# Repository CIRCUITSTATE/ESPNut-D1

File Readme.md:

# ESPNut-D1

[**ESPNut-D1**](https://github.com/CIRCUITSTATE/ESPNut-D1) (pronounced as **"ee yes peanut"**) is a single-channel USB-to-Serial converter and Auto-Programmer for the ESP32 & ESP8266 series microcontrollers from Espressif. While there exists many such programmers, ESPNut-D1 is a completely open-source hardware (OSHW) project designed in the **KiCad** open-source EDA tool. **D1** is the first design variant of this project. You can download the source files of this design, modify them and redistribute them as you wish.

ESPNut-D1 is based on the popular **CH340** series USB-to-Serial converter chip from *WCH*. The serial port of the chip connects to the target microcontroller through its own serial port. Thanks to the built-in serial bootloader of the ESP series microcontrollers, you can effortlessly program them at any time. The ESPNut-D1 makes this process a bit more convenient.

## Features

- CH340C/CH340G USB-to-Serial converter chip.
  - No external crystal required for the CH340C.
- USB-C connector with extra solderpads.
- Auto bootloader and reset circuit. Control both functions from the USB.
- Dedicated push-buttons for target reset and boot mode.
- 3.6~12V in, 3.3V out, 500 mA LDO.
- Slide switch for target power control.
- Target power control through load switch.
- SPDT slide switch for target voltage selection. Select between 3.3V and 5V.
- VBUS and target power indication LEDs.
- UART activity LEDs for both `TX` and `RX` lines.
- Dedicated push-button for power control of the target. Useful for boards without reset pin.
- 6-pin ESP-PROG 1.27 mm header.
- 6-pin JST-SH connector and solderpad for target ESP.
- 2x M2 mounting holes.

## Design

- **Parent Project:** ESPNut
- **Variant:** [ESPNut-D1](https://github.com/CIRCUITSTATE/ESPNut-D1)
- **Author:** Vishnu Mohanan (@vishnumaiea)
- **Latest Revision:** `R0.4`
- **Layer Count:** 2
- **Thickness:** 1.6 mm
- **Dimensions:** 44 x 20 mm
- **EDA Tool:** KiCad V9
- **License:** MIT

## Contributing

If you would like to contribute this project, you are welcome to post issues and feature requests on the **Issues** page. If you fork this project and created a new variant, you can let us know about it and get a unique identifier assigned for your project. The ID takes the following form.

```
Y<digit><letter><digit>
```

`Y` – Constant prefix.

`<digit>` – Digits from 0–9

`<letter>` – Characters from A–Z.

**Examples:**

```
Y1A1
Y1A2
Y2B1
Y3C4
```

The forked project should then be renamed to `ESPNut-D1-<ID>` form.

**Guidelines:**

- IDs are assigned upon request. You can create a new issue to request a new ID once a fork is created. Keep the issue title as `Request New ID` and include a link to your fork in the description.
- You can either request a new ID that you like and that is already not chosen, or allow us to choose an ID for you.
- You should rename the original source files with the `ESPNut-D1-<ID>` format.
- On the PCB, you can place the name of the project as `ESPNut-D1` and keep the ID as a standalone text on any visible layers.
- Once a unique ID is assigned to a forked project, the revision should be reset to `R0.1`. Do not keep the original revision of the project.

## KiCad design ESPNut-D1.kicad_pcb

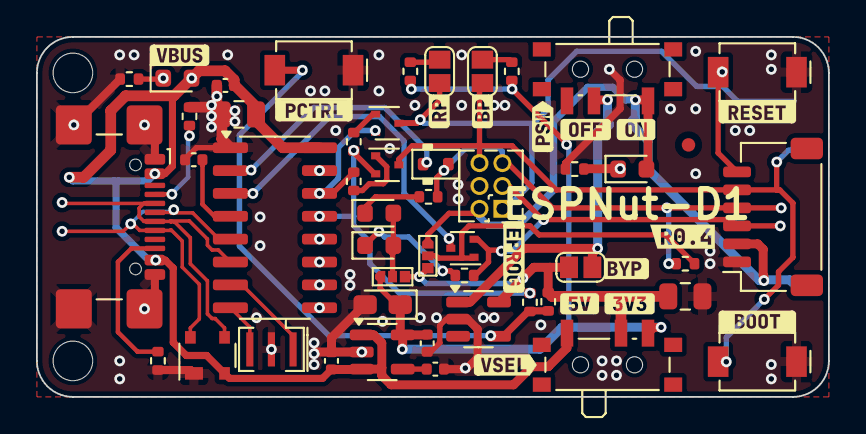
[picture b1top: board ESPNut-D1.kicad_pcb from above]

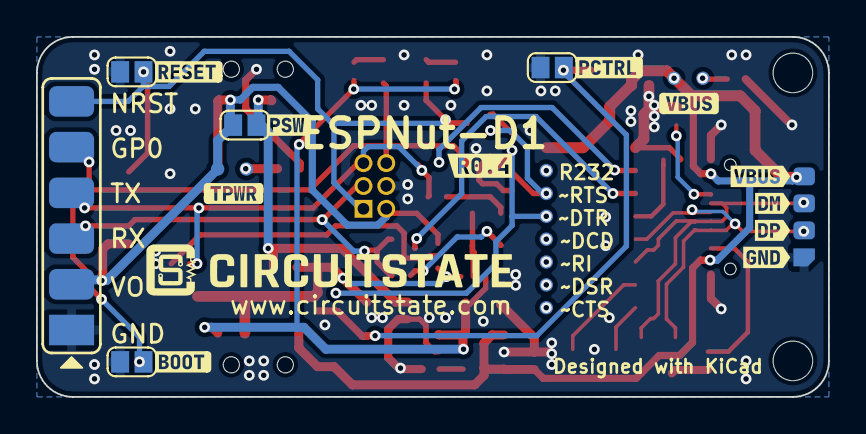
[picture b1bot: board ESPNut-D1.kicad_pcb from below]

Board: 2 copper layers, 44.0 x 20.0 mm, 93 parts (28 on the bottom side), 38 nets.

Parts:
C1, C8: 47uF; C_0805_2012Metric
C2, C3: 0.1uF; C_0402_1005Metric
C4, C7: 4.7uF; C_0402_1005Metric
C5: 470pF; C_0402_1005Metric
C6: 2.2uF; CP_EIA-2012-12_Kemet-R_Pad1.30x1.05mm_HandSolder
D1: VBUS_LED; LED_0603_1608Metric
D2: BAS70K; D_SOD-523
D3: SP0503BAHT; SOT-143
D4: ESP_PWR; LED_0603_1608Metric
D5: RX_LED; LED_0603_1608Metric
D6: TX_LED; LED_0603_1608Metric
FD1: Fiducial_0.75mm_Mask1.5mm
H1, H2: Mounting Hole; MountingHole_2.2mm_M2_DIN965
J1: USB_C_Receptacle_USB2.0; USB_C_Receptacle_GCT_USB4110
J2: ESP_CONN; Solderpad_1x06_P2.54mm_Rounded_Rectangle
J3: ESP_CONN; JST_SH_SM06B-SRSS-TB_1x06-1MP_P1.00mm_Horizontal
J4: USB_PADS; Solderpad_1x4_Rectangular_Rounded_1.2x1mm_P1.5mm
J5: ESP_PROG; PinHeader_2x03_P1.27mm_Vertical
JP1: RST_PUE; Solder-Jumper-1x2_P1.3mm_Open_Rounded_1.0x1.2mm
JP2: BT_PUE; Solder-Jumper-1x2_P1.3mm_Open_Rounded_1.0x1.2mm
JP3: TRX-PUV; Solder-Jumper_1x3_0402_Open
JP4: ESP_RST; Solder-Jumper-1x2_P1.3mm_Open_Rounded_1.0x1.2mm
JP5: ESP_BOOT; Solder-Jumper-1x2_P1.3mm_Open_Rounded_1.0x1.2mm
JP6: VDD_CTRL_BYP; Solder-Jumper-1x2_P1.3mm_Open_Rounded_1.0x1.2mm
JP7: ESP_VDD_SW; Solder-Jumper-1x2_P1.3mm_Open_Rounded_1.0x1.2mm
JP8: POW_CTRL; Solder-Jumper-1x2_P1.3mm_Open_Rounded_1.0x1.2mm
JP9: ACT-LED-V; Solder-Jumper_1x3_0402_Open
Q1, Q3: MMBT3904T-7-F; SOT-523
Q2: 2SK3019-TP; SOT-523
R1, R10, R12: 220R; R_0402_1005Metric
R2, R6: 5.1K; R_0402_1005Metric
R3, R4, R5, R7, R8, R9: 10K; R_0402_1005Metric
R13, R14: 1K; R_0402_1005Metric
SW1: ESP_RST; CK_SW_SPST_UK-B0273-SP25Y
SW2: ESP_BOOT; CK_SW_SPST_UK-B0273-SP25Y
SW3: ESP_VDD_SW; SW_SPDT_PCM12
SW4: ESPV_SEL; SW_SPDT_PCM12
SW5: POW_CTRL; CK_SW_SPST_UK-B0273-SP25Y
TP1: VBUS; TestPoint-0.75mm
TP2: VBUS_LED_1; TestPoint-0.75mm
TP3: R232; TestPoint-0.75mm
TP4: CTS; TestPoint-0.75mm
TP5: DSR; TestPoint-0.75mm
TP6: RI; TestPoint-0.75mm
TP7: DCD; TestPoint-0.75mm
TP8: DTR; TestPoint-0.75mm
TP9: RTS; TestPoint-0.75mm
TP10: ESP_VDD_O; TestPoint-0.75mm
TP11: ESP_PWR_1; TestPoint-0.75mm
U1: CH340G; SOIC-16_3.9x9.9mm_P1.27mm
U2: MIC5219-3.3YM5; SOT-23-5
U3: AP22804AW5; SOT-23-5
Y1: 12MHz; Resonator_SMD_Murata_CSTxExxV-3Pin_3.0x1.1mm
kibuzzard-67F0B0FE: G***; kibuzzard-67F0B0FE
kibuzzard-67F0B154: G***; kibuzzard-67F0B154
kibuzzard-67F0B222, kibuzzard-67F0B222#2: G***; kibuzzard-67F0B222
kibuzzard-67F0C2BD: G***; kibuzzard-67F0C2BD
kibuzzard-67F0C2E8: G***; kibuzzard-67F0C2E8
kibuzzard-67F0C30C: G***; kibuzzard-67F0C30C
kibuzzard-67F0C300: G***; kibuzzard-67F0C300
kibuzzard-67F0C318: G***; kibuzzard-67F0C318
kibuzzard-690A4E8D: G***; kibuzzard-690A4E8D
kibuzzard-690A4E32: G***; kibuzzard-690A4E32
kibuzzard-690A4E84: G***; kibuzzard-690A4E84
kibuzzard-68837A0C: G***; kibuzzard-68837A0C
kibuzzard-68837ACD: G***; kibuzzard-68837ACD
kibuzzard-68837FCA: G***; kibuzzard-68837FCA
kibuzzard-688268B9: G***; kibuzzard-688268B9
kibuzzard-688269BA: G***; kibuzzard-688269BA
kibuzzard-688269D8: G***; kibuzzard-688269D8
kibuzzard-688272B9: G***; kibuzzard-688272B9
kibuzzard-688272CF: G***; kibuzzard-688272CF
kibuzzard-688273BB: G***; kibuzzard-688273BB
kibuzzard-6882689F: G***; kibuzzard-6882689F
kibuzzard-68826928: G***; kibuzzard-68826928
kibuzzard-68826931: G***; kibuzzard-68826931
kibuzzard-68827414: G***; kibuzzard-68827414
kibuzzard-68827490: G***; kibuzzard-68827490

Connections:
+3V3: C6.1, C7.1, JP9.1 (A), R4.1, R5.1, SW4.3 (C), U2.5 (OUT)
/CH_RX: J2.3, J3.3, J5.3, Q2.2 (S), R14.2
/CH_TX: D2.2 (A), J2.4, J3.4, J5.5, R3.2, R13.2
/DTR: Q3.2 (E), R7.2, R10.2, TP8.1, U1.13 (~DTR)
/ESP_IO0: J2.5, J3.5, J5.6, JP2.1 (A), JP5.2 (B), Q3.3 (C), SW2.2
/ESP_NRST: J2.6, J3.6, J5.1, JP1.1 (A), JP4.2 (B), Q1.3 (C), SW1.2
/ESP_VDD_I: C8.1, JP3.3 (B), JP6.2 (B), JP9.3 (B), R9.2, SW4.2 (B), U3.5 (IN)
/ESP_VDD_O: D4.2 (A), J2.2, J3.2, J5.2, JP3.1 (A), JP7.1 (A), SW3.1 (A), TP10.1
/RTS: Q1.2 (E), R8.2, TP9.1, U1.14 (~RTS)
/USB_D+: D3.4 (K), J1.A6 (D+), J1.B6 (D+), J4.2, U1.5 (UD+)
/USB_D-: D3.3 (K), J1.A7 (D-), J1.B7 (D-), J4.3, U1.6 (UD-)
/V3: C2.1, U1.4 (V3)
GND: C1.1, C2.2, C3.2, C4.2, C5.2, C6.2, C7.2, C8.2, D3.1 (A), J1.A1 (GND), J1.A12 (GND), J1.B1 (GND), J1.B12 (GND), J1.S1 (SHIELD), J2.1, J3.1, J4.1, J5.4, JP4.1 (A), JP5.1 (A), JP8.1 (A), R1.1, R2.2, R6.2, R12.1, SW1.1, SW2.1, SW5.1, U1.1 (GND), U2.2 (GND), U3.2 (GND), Y1.2
unnamed: D1.1 (K), R1.2, TP2.1
unnamed: D2.1 (K), U1.2 (TXD)
unnamed: D4.1 (K), R12.2, TP11.1
unnamed: D5.2 (A), D6.2 (A), JP9.2 (C)
unnamed: D5.1 (K), R13.1
unnamed: D6.1 (K), R14.1
unnamed: J1.A5 (CC1), R2.1
unnamed: J1.B5 (CC2), R6.1
unnamed: JP1.2 (B), R4.2
unnamed: JP2.2 (B), R5.2
unnamed: JP3.2 (C), Q2.1 (G), R3.1
unnamed: JP6.1 (A), JP7.2 (B), SW3.2 (B), U3.1 (OUT)
unnamed: JP8.2 (B), R9.1, R10.1, SW5.2, U3.4 (EN)
unnamed: Q1.1 (B), R7.1
unnamed: Q2.3 (D), U1.3 (RXD)
unnamed: Q3.1 (B), R8.1
unnamed: TP3.1, U1.15 (R232)
unnamed: U1.7 (XI), Y1.1
unnamed: U1.8 (XO), Y1.3
unnamed: TP4.1, U1.9 (~CTS)
unnamed: TP7.1, U1.12 (~DCD)
unnamed: TP5.1, U1.10 (~DSR)
unnamed: TP6.1, U1.11 (~RI)
unnamed: C5.1, U2.4 (BP)
VBUS: C1.2, C3.1, C4.1, D1.2 (A), D3.2 (K), J1.A4 (VBUS), J1.A9 (VBUS), J1.B4 (VBUS), J1.B9 (VBUS), J4.4, SW4.1 (A), TP1.1, U1.16 (VCC), U2.1 (IN), U2.3 (EN)

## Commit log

2024-08-26 R0.1 Initial Commit
    * Added net classes and highlights.
    * Added Changes and Readme.
    * Added `.gitignore`.
    * New Revision `R0.1`.
2025-04-04 Updated project version to KiCad V9
    - Updated text colors.
2025-04-05 Placement completed
    - Added breakout pads for the LEDs.
    - Changed USB-C connector footprint to SMD one.
    - Added PCB outline.
    - Placed all components.
    - Added silkscreen labels and logos.
    - Routing pending.
2025-04-08 Routing completed
    - Added GND zones.
    - DRC passes.
    - Added more silkscreen labels.
    - Added CIRCUITSTATE logo on the back silkscreen.
    - Updated Fab layers.
2025-04-08 Updated BoM
    - Updated BoM.
    - Assigned all MPNs.
    - Changed the 10 uF, 0402 capacitor to 4.7 uF, 0402.
    - Imported all changes to the PCB.
2025-04-09 Generated manufacturing files
    - Added KiExport configuration and script.
    - Added dimension drawings.
    - Added board characteristics and stackup table.
    - Added `OSHW` logo.
2025-04-12 Generated new manufacturing files
    - Updated Readme.
2025-04-23 Added fiducial
    - Added fiducial to the front side.
    - Generated new manufacturing files.
    - Updated Readme.
2025-07-24 New Revision `R0.2`
    - Schematic
    - Deleted the Mosfet based power control circuit.
    - Replaced it with `AP22804AW5` based circuit.
    - Not because it is not working, but because a proper load switch is more reliable.
    - Added 6-pin `SM06B-SRSS-TB` JST-SH connector for target ESP.
    - The THT pin-headers will be changes to SMD one and placed on the back side.
2025-07-25 Routing completed
    - Schematic
    - Updated BoM.
    - Reset the annotations.
    - PCB
    - Imported all changes to the PCB.
    - Routing completed.
2025-07-25 Generated manufacturing files
    - Updated KiExport configuration to `v1.7`.
    - Generated manufacturing files.
2025-08-02 New Revision `R0.3` - Schematic - Added DPDT `UART_SWAP` switch to swap the `TX` and `RX` lines. - But this is DNPed because the switch consumes too much space. - Added UART activity LEDs on both `TX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
2025-08-02 Updated BoM
    - Updated BoM.
    - Fixed UART activity LEDs MPNs.
    - Generated new manufacturing files.
2025-11-04 Added `47 uF` 0805 capacitors
    - Schematic
    - Added `47 uF` 0805 capacitors to the VBUS line, near the CH340 and `ESP_VDD_I`.
    - This was required because it was observed that the CH340 will reset when a significant load is connected to the `VBUS` line.
    - Adding two 22 uF capacitors proved to solve the issue.
    - But we are going to use 47 uF capacitors for better stability.
    - PCB
2025-11-05 New Revision 🆕 `R0.4`
    - Schematic
    - Removed the PNP transistors from the UART activity LED circuit.
    - The SparkFun Serial Basic directly connects the LEDs to the TX and RX lines via `1K` resistors.
    - We will do the same.
    - But the voltage supplied to the LEDs can be set using a jumper `ACT-LED-V`.
    - Added jumper `TRX-PUV` to the CH340 communication lines.
2025-11-07 Changed all via sizes to `0.6/0.3 mm`
    - Changed all via sizes to `0.6/0.3 mm` to comply with Lion Circuits.
    - Generated new manufacturing files.
